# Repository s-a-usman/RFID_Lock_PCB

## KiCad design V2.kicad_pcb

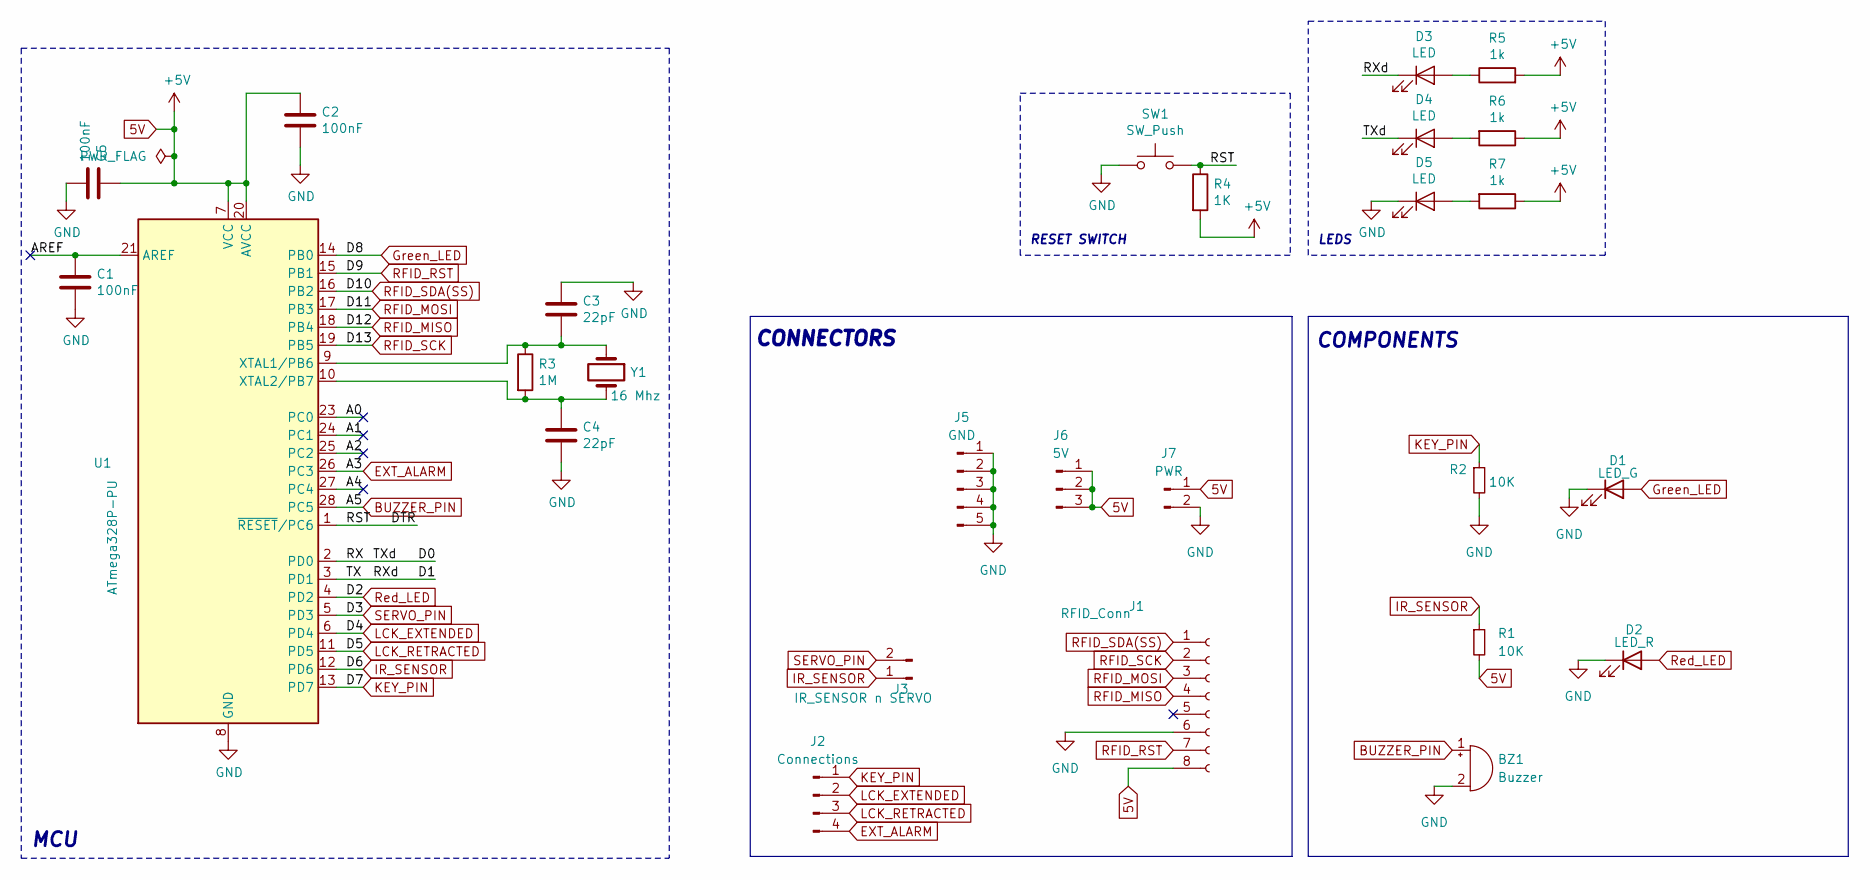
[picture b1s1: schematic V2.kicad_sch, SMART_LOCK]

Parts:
BZ1: Buzzer; MagneticBuzzer_Kingstate_KCG0601
C1, C2, C5: 100nF; CP_Radial_D5.0mm_P2.50mm
C3, C4: 22pF; CP_Radial_D5.0mm_P2.50mm
D1: LED_G; LED_D5.0mm_Clear
D2: LED_R; LED_D5.0mm
D3, D4, D5: LED; LED_0805_2012Metric
J1: RFID_Conn; PinSocket_1x08_P2.54mm_Vertical
J2: Connections; PinHeader_1x04_P2.54mm_Vertical
J3: IR_SENSOR n SERVO; PinHeader_1x02_P2.54mm_Vertical
J5: GND; PinHeader_1x05_P2.54mm_Vertical
J6: 5V; PinHeader_1x03_P2.54mm_Vertical
J7: PWR; PinHeader_1x02_P2.54mm_Vertical
R1, R2: 10K; R_Axial_DIN0207_L6.3mm_D2.5mm_P7.62mm_Horizontal
R3: 1M; R_Axial_DIN0207_L6.3mm_D2.5mm_P7.62mm_Horizontal
R4: 1K; R_Axial_DIN0207_L6.3mm_D2.5mm_P7.62mm_Horizontal
R5, R6, R7: 1k; R_0805_2012Metric
SW1: SW_Push; SW_SPST_B3U-1000P-B
U1: ATmega328P-PU; DIP-28_W7.62mm_Socket_LongPads
Y1: 16 Mhz; Crystal_HC49-4H_Vertical

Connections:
5V: C2.1, C5.1, J1.8, J6.1, J6.2, J6.3, J7.1, R1.2, R4.2, R5.2, R6.1, R7.1, U1.7 (VCC), U1.20 (AVCC)
/A0: U1.23 (PC0)
/A1: U1.24 (PC1)
/A2: U1.25 (PC2)
/A4: U1.27 (PC4)
/AREF: C1.1, U1.21 (AREF)
/D0: D4.1 (K), U1.2 (PD0)
/D1: D3.1 (K), U1.3 (PD1)
/DTR: R4.1, SW1.2, U1.1 (~RESET/PC6)
BUZZER_PIN: BZ1.1 (+), U1.28 (PC5)
EXT_ALARM: J2.4, U1.26 (PC3)
GND: BZ1.2 (-), C1.2, C2.2, C3.1, C4.2, C5.2, D1.1 (K), D2.1 (K), D5.1 (K), J1.6, J5.1, J5.2, J5.3, J5.4, J5.5, J7.2, R2.2, SW1.1, U1.8 (GND), U1.22 (GND)
Green_LED: D1.2 (A), U1.14 (PB0)
IR_SENSOR: J3.1, R1.1, U1.12 (PD6)
KEY_PIN: J2.1, R2.1, U1.13 (PD7)
LCK_EXTENDED: J2.2, U1.6 (PD4)
LCK_RETRACTED: J2.3, U1.11 (PD5)
unnamed: D3.2 (A), R5.1
unnamed: D4.2 (A), R6.2
unnamed: D5.2 (A), R7.2
unnamed: C3.2, R3.1, U1.9 (XTAL1/PB6), Y1.1
unnamed: C4.1, R3.2, U1.10 (XTAL2/PB7), Y1.2
RFID_MISO: J1.4, U1.18 (PB4)
RFID_MOSI: J1.3, U1.17 (PB3)
RFID_RST: J1.7, U1.15 (PB1)
RFID_SCK: J1.2, U1.19 (PB5)
RFID_SDA(SS): J1.1, U1.16 (PB2)
Red_LED: D2.2 (A), U1.4 (PD2)
SERVO_PIN: J3.2, U1.5 (PD3)

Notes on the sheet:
LEDS
CONNECTORS
COMPONENTS
MCU
RESET SWITCH

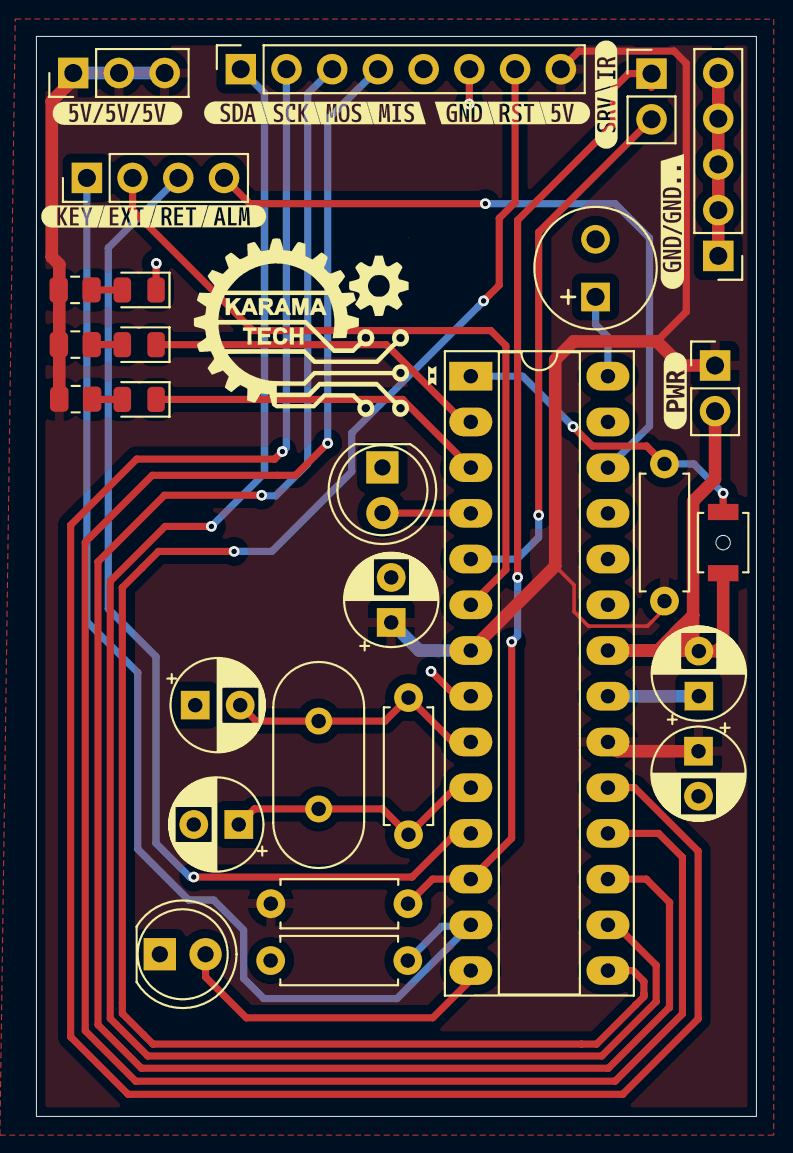
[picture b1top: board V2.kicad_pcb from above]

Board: 2 copper layers, 40.0 x 60.0 mm, 44 parts (0 on the bottom side), 25 nets.

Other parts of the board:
kibuzzard-674B2C7F: G***; kibuzzard-674B2C7F
kibuzzard-674B2CD4: G***; kibuzzard-674B2CD4
kibuzzard-674B2E7C: G***; kibuzzard-674B2E7C
kibuzzard-674B2E9A: G***; kibuzzard-674B2E9A
kibuzzard-674B2EE4: G***; kibuzzard-674B2EE4
kibuzzard-674B2EF3: G***; kibuzzard-674B2EF3
kibuzzard-674B2F0D: G***; kibuzzard-674B2F0D
kibuzzard-674B2F1D: G***; kibuzzard-674B2F1D
kibuzzard-674B2F69: G***; kibuzzard-674B2F69
kibuzzard-674B20BC: G***; kibuzzard-674B20BC
kibuzzard-674B20CA: G***; kibuzzard-674B20CA
kibuzzard-674B41C3: G***; kibuzzard-674B41C3
kibuzzard-674B218C: G***; kibuzzard-674B218C
kibuzzard-674B266F: G***; kibuzzard-674B266F
kibuzzard-674B267A: G***; kibuzzard-674B267A
kibuzzard-674B2007: G***; kibuzzard-674B2007
kibuzzard-674B2203: G***; kibuzzard-674B2203

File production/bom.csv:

Designator,Footprint,Quantity,Value,LCSC Part #
BZ1,MagneticBuzzer_Kingstate_KCG0601,1,Buzzer,
"C1, C2, C5",CP_Radial_D5.0mm_P2.50mm,3,100nF,
"C3, C4",CP_Radial_D5.0mm_P2.50mm,2,22pF,
D1,LED_D5.0mm_Clear,1,LED_G,
D2,LED_D5.0mm,1,LED_R,
"D3, D4, D5",0805,3,LED,
J1,PinSocket_1x08_P2.54mm_Vertical,1,RFID_Conn,
J2,PinHeader_1x04_P2.54mm_Vertical,1,Connections,
J3,PinHeader_1x02_P2.54mm_Vertical,1,IR_SENSOR n SERVO,
J5,PinHeader_1x05_P2.54mm_Vertical,1,GND,
J6,PinHeader_1x03_P2.54mm_Vertical,1,5V,
J7,PinHeader_1x02_P2.54mm_Vertical,1,PWR,
"R1, R2",R_Axial_DIN0207_L6.3mm_D2.5mm_P7.62mm_Horizontal,2,10K,
R3,R_Axial_DIN0207_L6.3mm_D2.5mm_P7.62mm_Horizontal,1,1M,
R4,R_Axial_DIN0207_L6.3mm_D2.5mm_P7.62mm_Horizontal,1,1K,
"R5, R6, R7",0805,3,1k,
SW1,SW_SPST_B3U-1000P-B,1,SW_Push,
U1,DIP-28_W7.62mm_Socket_LongPads,1,ATmega328P-PU,
Y1,Crystal_HC49-4H_Vertical,1,16 Mhz,

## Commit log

2024-11-07 Hardware design files in KiCad
2024-12-13 Add BOM
